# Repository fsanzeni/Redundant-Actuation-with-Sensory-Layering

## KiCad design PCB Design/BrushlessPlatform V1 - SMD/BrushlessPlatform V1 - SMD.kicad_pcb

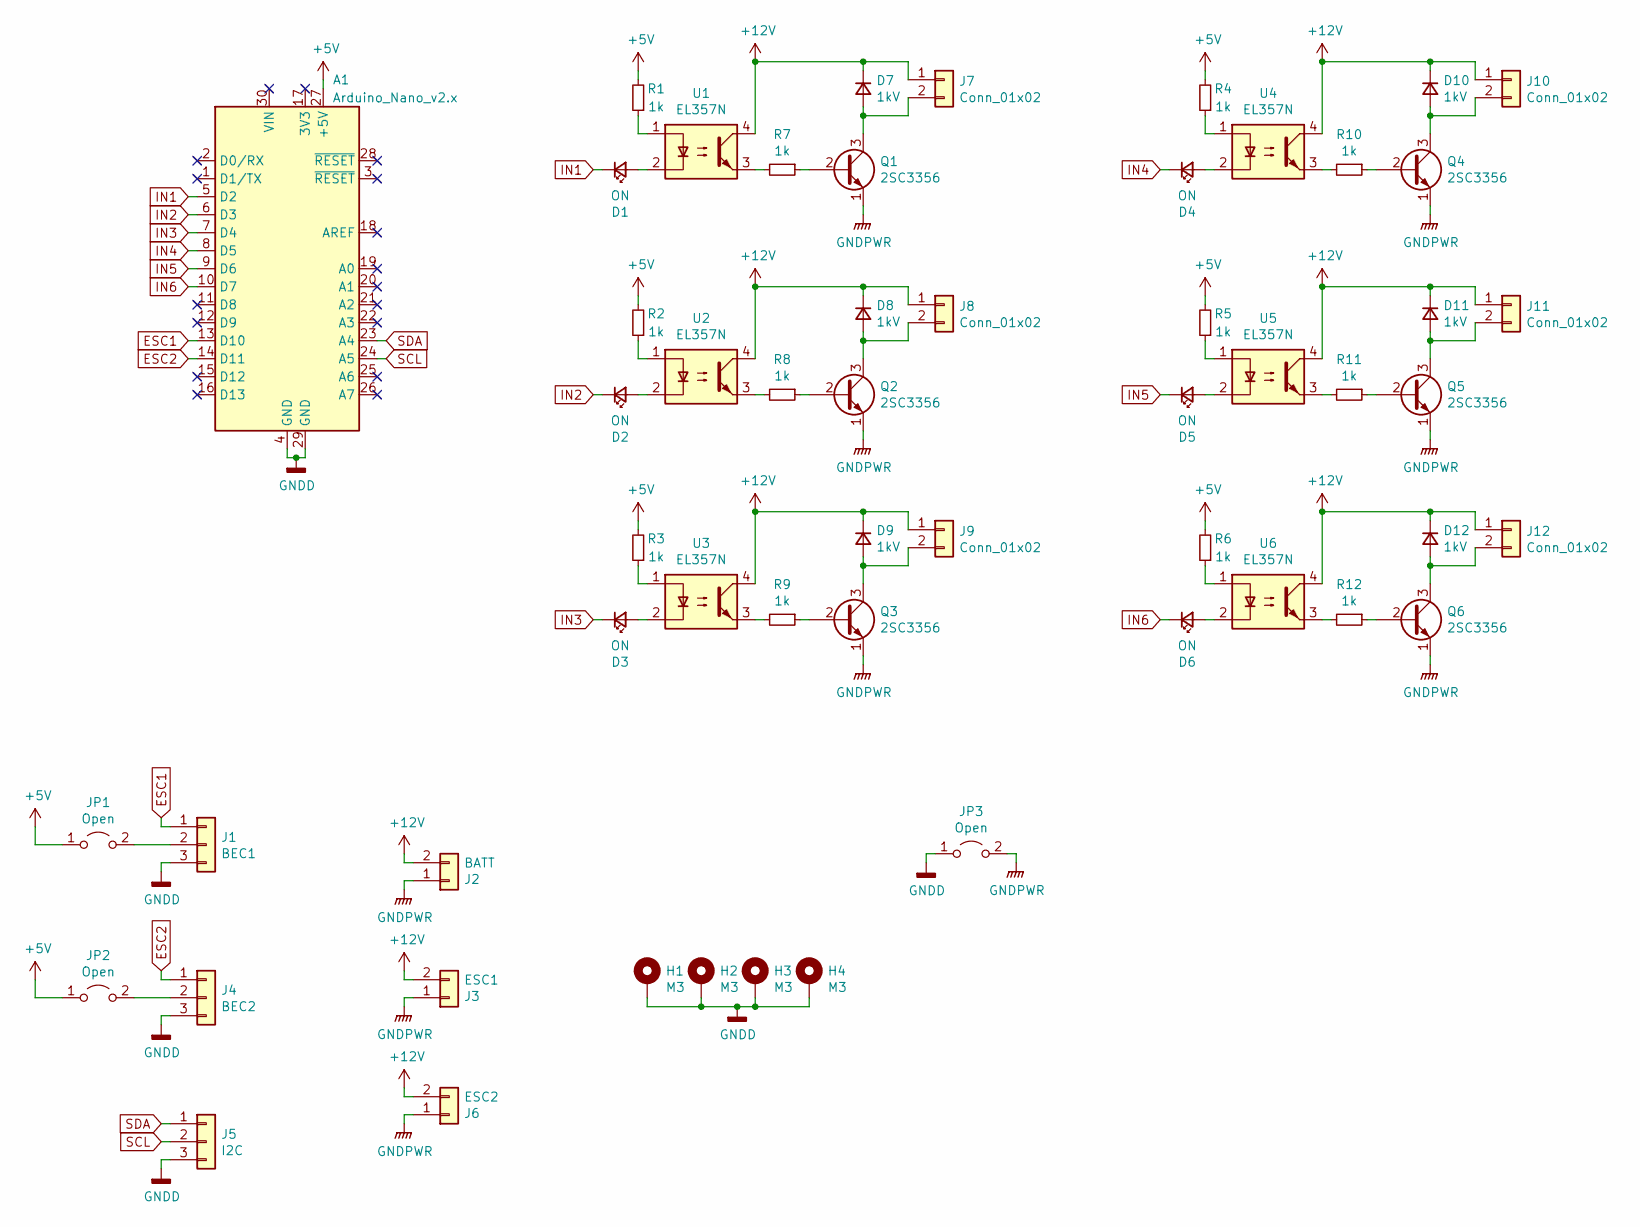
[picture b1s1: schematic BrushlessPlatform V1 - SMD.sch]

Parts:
A1: Arduino_Nano_v2.x; Arduino_Nano
D1, D2, D3, D4, D5, D6: ON; LED_0603_1608Metric
D7, D8, D9, D10, D11, D12: 1kV; D_SMA
H1, H2, H3, H4: M3; MountingHole_3.2mm_M3_ISO7380_Pad
J1: BEC1; PinSocket_1x03_P2.54mm_Vertical
J2: BATT; AMASS_XT60-M_1x02_P7.20mm_Vertical
J3: ESC1; AMASS_XT60-M_1x02_P7.20mm_Vertical
J4: BEC2; PinSocket_1x03_P2.54mm_Vertical
J5: I2C; PinSocket_1x03_P2.54mm_Vertical
J6: ESC2; AMASS_XT60-M_1x02_P7.20mm_Vertical
J7, J8, J9, J10, J11, J12: Conn_01x02; SolderWire-0.75sqmm_1x02_P4.8mm_D1.25mm_OD2.3mm_Relief
JP1, JP2, JP3: Open; SolderJumper-2_P1.3mm_Open_Pad1.0x1.5mm
Q1, Q2, Q3, Q4, Q5, Q6: 2SC3356; SOT-23
R1, R2, R3, R4, R5, R6, R7, R8, R9, R10, R11, R12: 1k; R_0603_1608Metric
U1, U2, U3, U4, U5, U6: EL357N; SOP-4_4.1x4.4x2.54P

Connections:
+5V: A1.27 (+5V), JP1.1 (A), JP2.1 (A), R1.2, R2.2, R3.2, R4.2, R5.2, R6.2
ESC1: A1.13 (D10), J1.1
ESC2: A1.14 (D11), J4.1
GNDD: A1.4 (GND), A1.29 (GND), H1.1, H2.1, H3.1, H4.1, J1.3, J4.3, J5.3, JP3.1 (A)
IN1: A1.5 (D2), D1.1 (K)
IN2: A1.6 (D3), D2.1 (K)
IN3: A1.7 (D4), D3.1 (K)
IN4: A1.8 (D5), D4.1 (K)
IN5: A1.9 (D6), D5.1 (K)
IN6: A1.10 (D7), D6.1 (K)
unnamed: D1.2 (A), U1.2
unnamed: D2.2 (A), U2.2
unnamed: D3.2 (A), U3.2
unnamed: D4.2 (A), U4.2
unnamed: D5.2 (A), U5.2
unnamed: D6.2 (A), U6.2
unnamed: D7.2 (A), J7.2, Q1.3 (C)
unnamed: D8.2 (A), J8.2, Q2.3 (C)
unnamed: D9.2 (A), J9.2, Q3.3 (C)
unnamed: D10.2 (A), J10.2, Q4.3 (C)
unnamed: D11.2 (A), J11.2, Q5.3 (C)
unnamed: D12.2 (A), J12.2, Q6.3 (C)
unnamed: J1.2, JP1.2 (B)
unnamed: J4.2, JP2.2 (B)
unnamed: Q1.2 (B), R7.1
unnamed: Q2.2 (B), R8.1
unnamed: Q3.2 (B), R9.1
unnamed: Q4.2 (B), R10.1
unnamed: Q5.2 (B), R11.1
unnamed: Q6.2 (B), R12.1
unnamed: R1.1, U1.1
unnamed: R2.1, U2.1
unnamed: R3.1, U3.1
unnamed: R4.1, U4.1
unnamed: R5.1, U5.1
unnamed: R6.1, U6.1
unnamed: R7.2, U1.3
unnamed: R8.2, U2.3
unnamed: R9.2, U3.3
unnamed: R10.2, U4.3
unnamed: R11.2, U5.3
unnamed: R12.2, U6.3
SCL: A1.24 (A5), J5.2
SDA: A1.23 (A4), J5.1

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
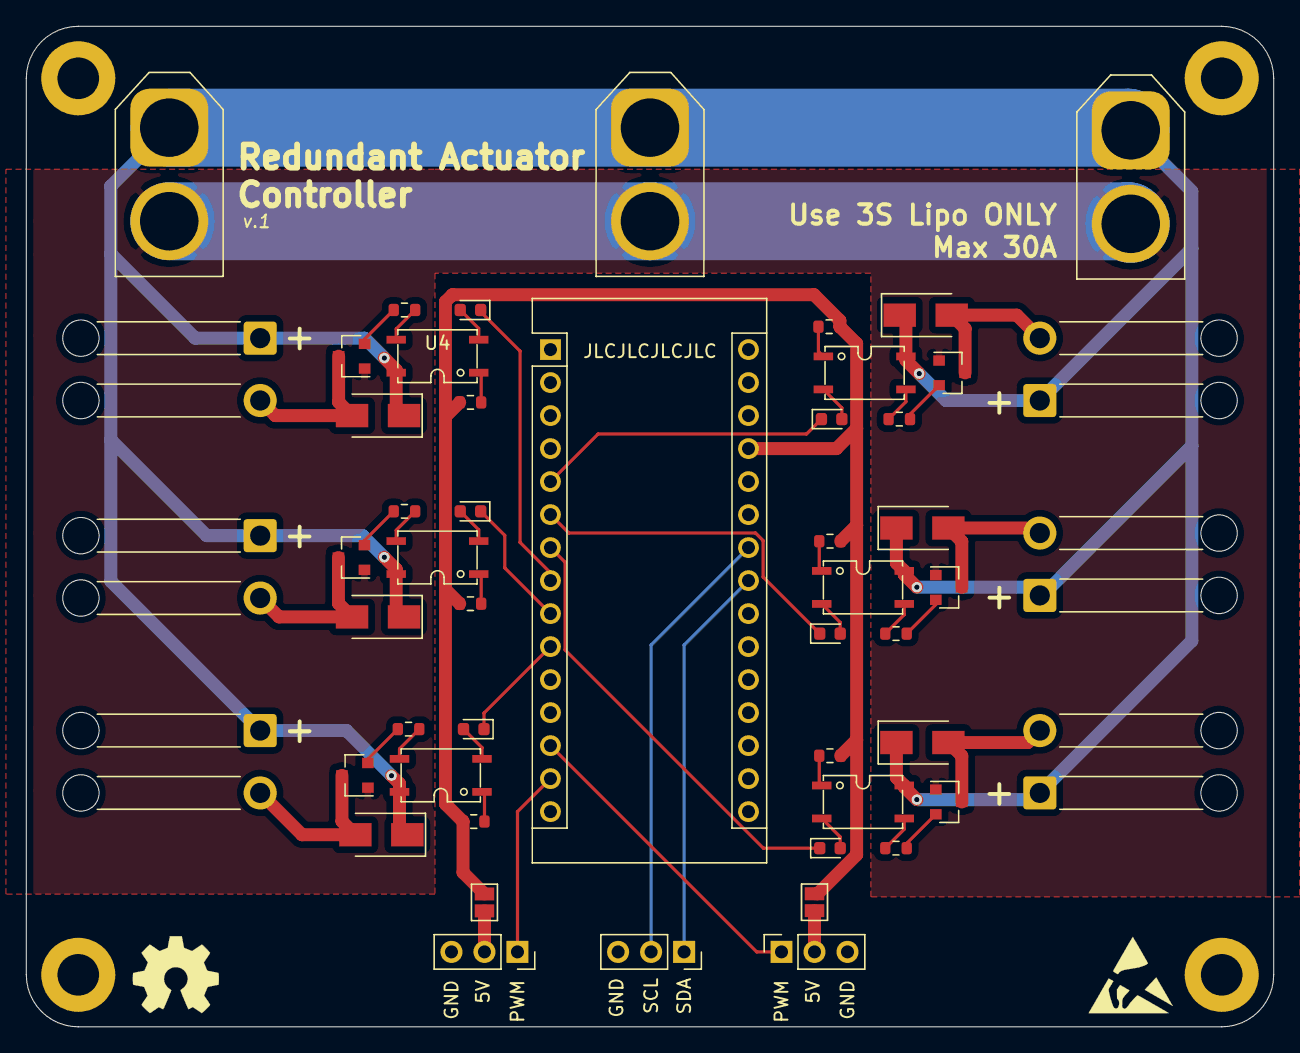
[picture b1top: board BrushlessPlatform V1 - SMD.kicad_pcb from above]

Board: 2 copper layers, 96.0 x 77.0 mm, 55 parts (0 on the bottom side), 46 nets.

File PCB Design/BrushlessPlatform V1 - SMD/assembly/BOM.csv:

Designator,Quantity,Value,Footprint,LCSC Part #,
"D1, D2, D3, D4, D5, D6, ",6,ON,0603,C72043,
"D7, D8, D9, D10, D11, D12, ",6,1kV,"SMA,DO-214AC",C412437,
"Q1, Q2, Q3, Q4, Q5, Q6, ",6,2SC3356,SOT-23-3,C9659,
"R1, R2, R3, R4, R5, R6, R7, R8, R9, R10, R11, R12, ",12,1k,0603,C21190,
"U1, U2, U3, U4, U5, U6, ",6,EL357N,SOP-4_4.1x4.4x2.54P,C6649,
,,,,,

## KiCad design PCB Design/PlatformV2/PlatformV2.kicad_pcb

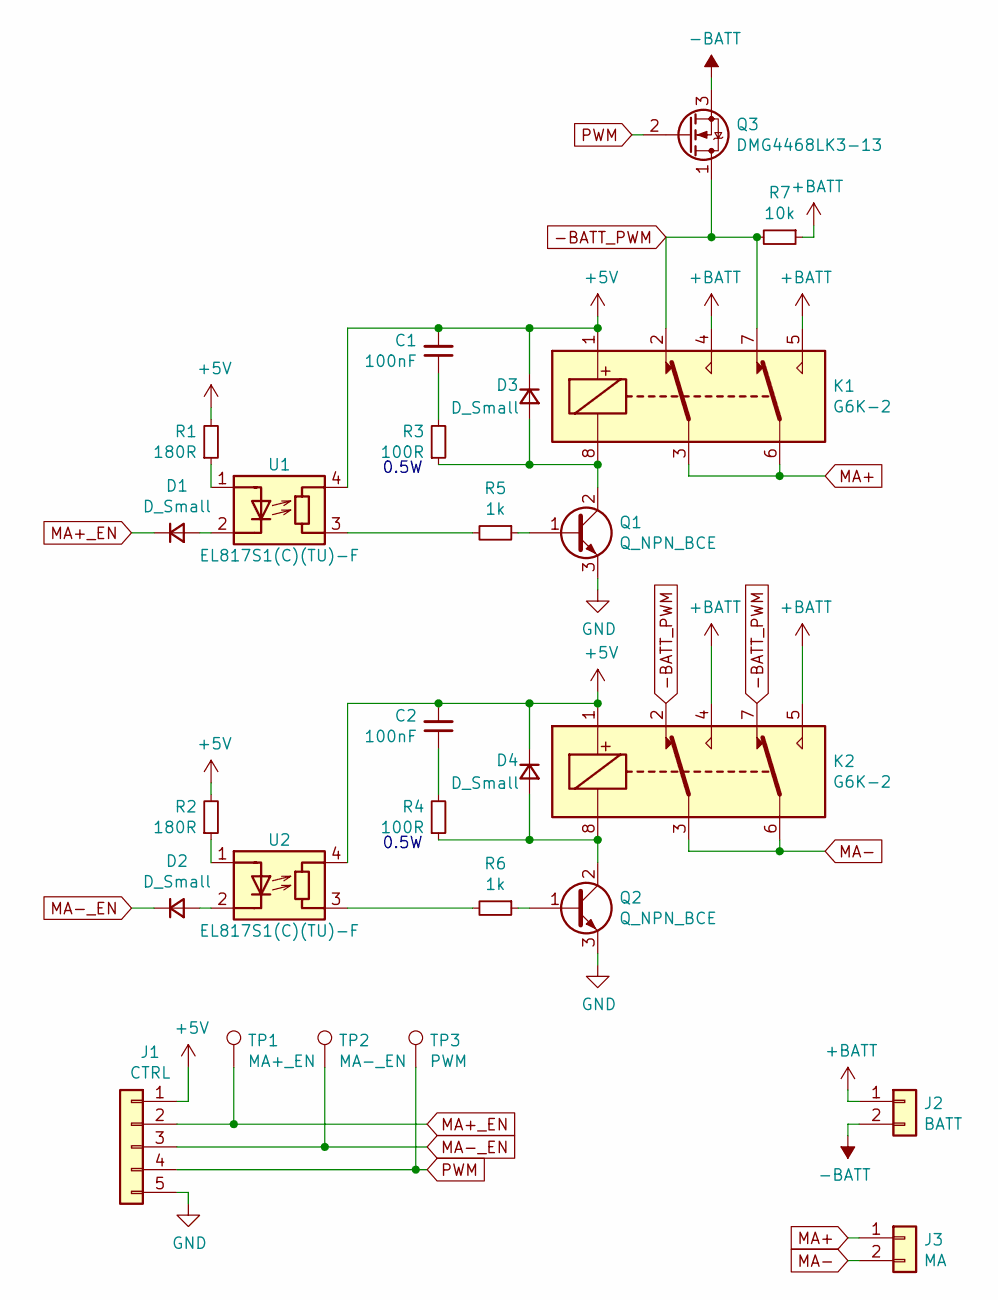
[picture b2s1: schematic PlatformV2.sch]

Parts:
C1, C2: 100nF; C_0805_2012Metric
D1, D2: D_Small; D_SOD-323F
D3, D4: D_Small; D_SMA
J1: CTRL; PinSocket_1x05_P2.54mm_Vertical
J2: BATT; PinSocket_1x02_P2.54mm_Vertical
J3: MA; PinSocket_1x02_P2.54mm_Vertical
K1, K2: G6K-2; G6K-2F_DC5
Q1, Q2: Q_NPN_BCE; SOT-23
Q3: DMG4468LK3-13; TO-252-2
R1, R2: 180R; R_0603_1608Metric
R3, R4: 100R; R_0603_1608Metric
R5, R6: 1k; R_0603_1608Metric
R7: 10k; R_0603_1608Metric
TP1: MA+_EN; TestPoint_Pad_D1.0mm
TP2: MA-_EN; TestPoint_Pad_D1.0mm
TP3: PWM; TestPoint_Pad_D1.0mm
U1, U2: EL817S1(C)(TU)-F

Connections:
+5V: C1.2, C2.2, D3.1 (K), D4.1 (K), J1.1, K1.1, K2.1, R1.2, R2.2, U1.4 (R), U2.4 (R)
+BATT: J2.1, K1.4, K1.5, K2.4, K2.5, R7.1
-BATT: J2.2, Q3.3 (S)
-BATT_PWM: K1.2, K1.7, K2.2, K2.7, Q3.1 (D), R7.2
GND: J1.5, Q1.3 (E), Q2.3 (E)
MA+: J3.1, K1.3, K1.6
MA+_EN: D1.1 (K), J1.2, TP1.1
MA-: J3.2, K2.3, K2.6
MA-_EN: D2.1 (K), J1.3, TP2.1
unnamed: C1.1, R3.2
unnamed: C2.1, R4.2
unnamed: D1.2 (A), U1.2 (K)
unnamed: D2.2 (A), U2.2 (K)
unnamed: D3.2 (A), K1.8, Q1.2 (C), R3.1
unnamed: D4.2 (A), K2.8, Q2.2 (C), R4.1
unnamed: Q1.1 (B), R5.1
unnamed: Q2.1 (B), R6.1
unnamed: R1.1, U1.1 (A)
unnamed: R2.1, U2.1 (A)
unnamed: R5.2, U1.3 (R)
unnamed: R6.2, U2.3 (R)
PWM: J1.4, Q3.2 (G), TP3.1

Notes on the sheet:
0.5W

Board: 2 copper layers, 26 parts (0 on the bottom side), 22 nets, no tracks yet.

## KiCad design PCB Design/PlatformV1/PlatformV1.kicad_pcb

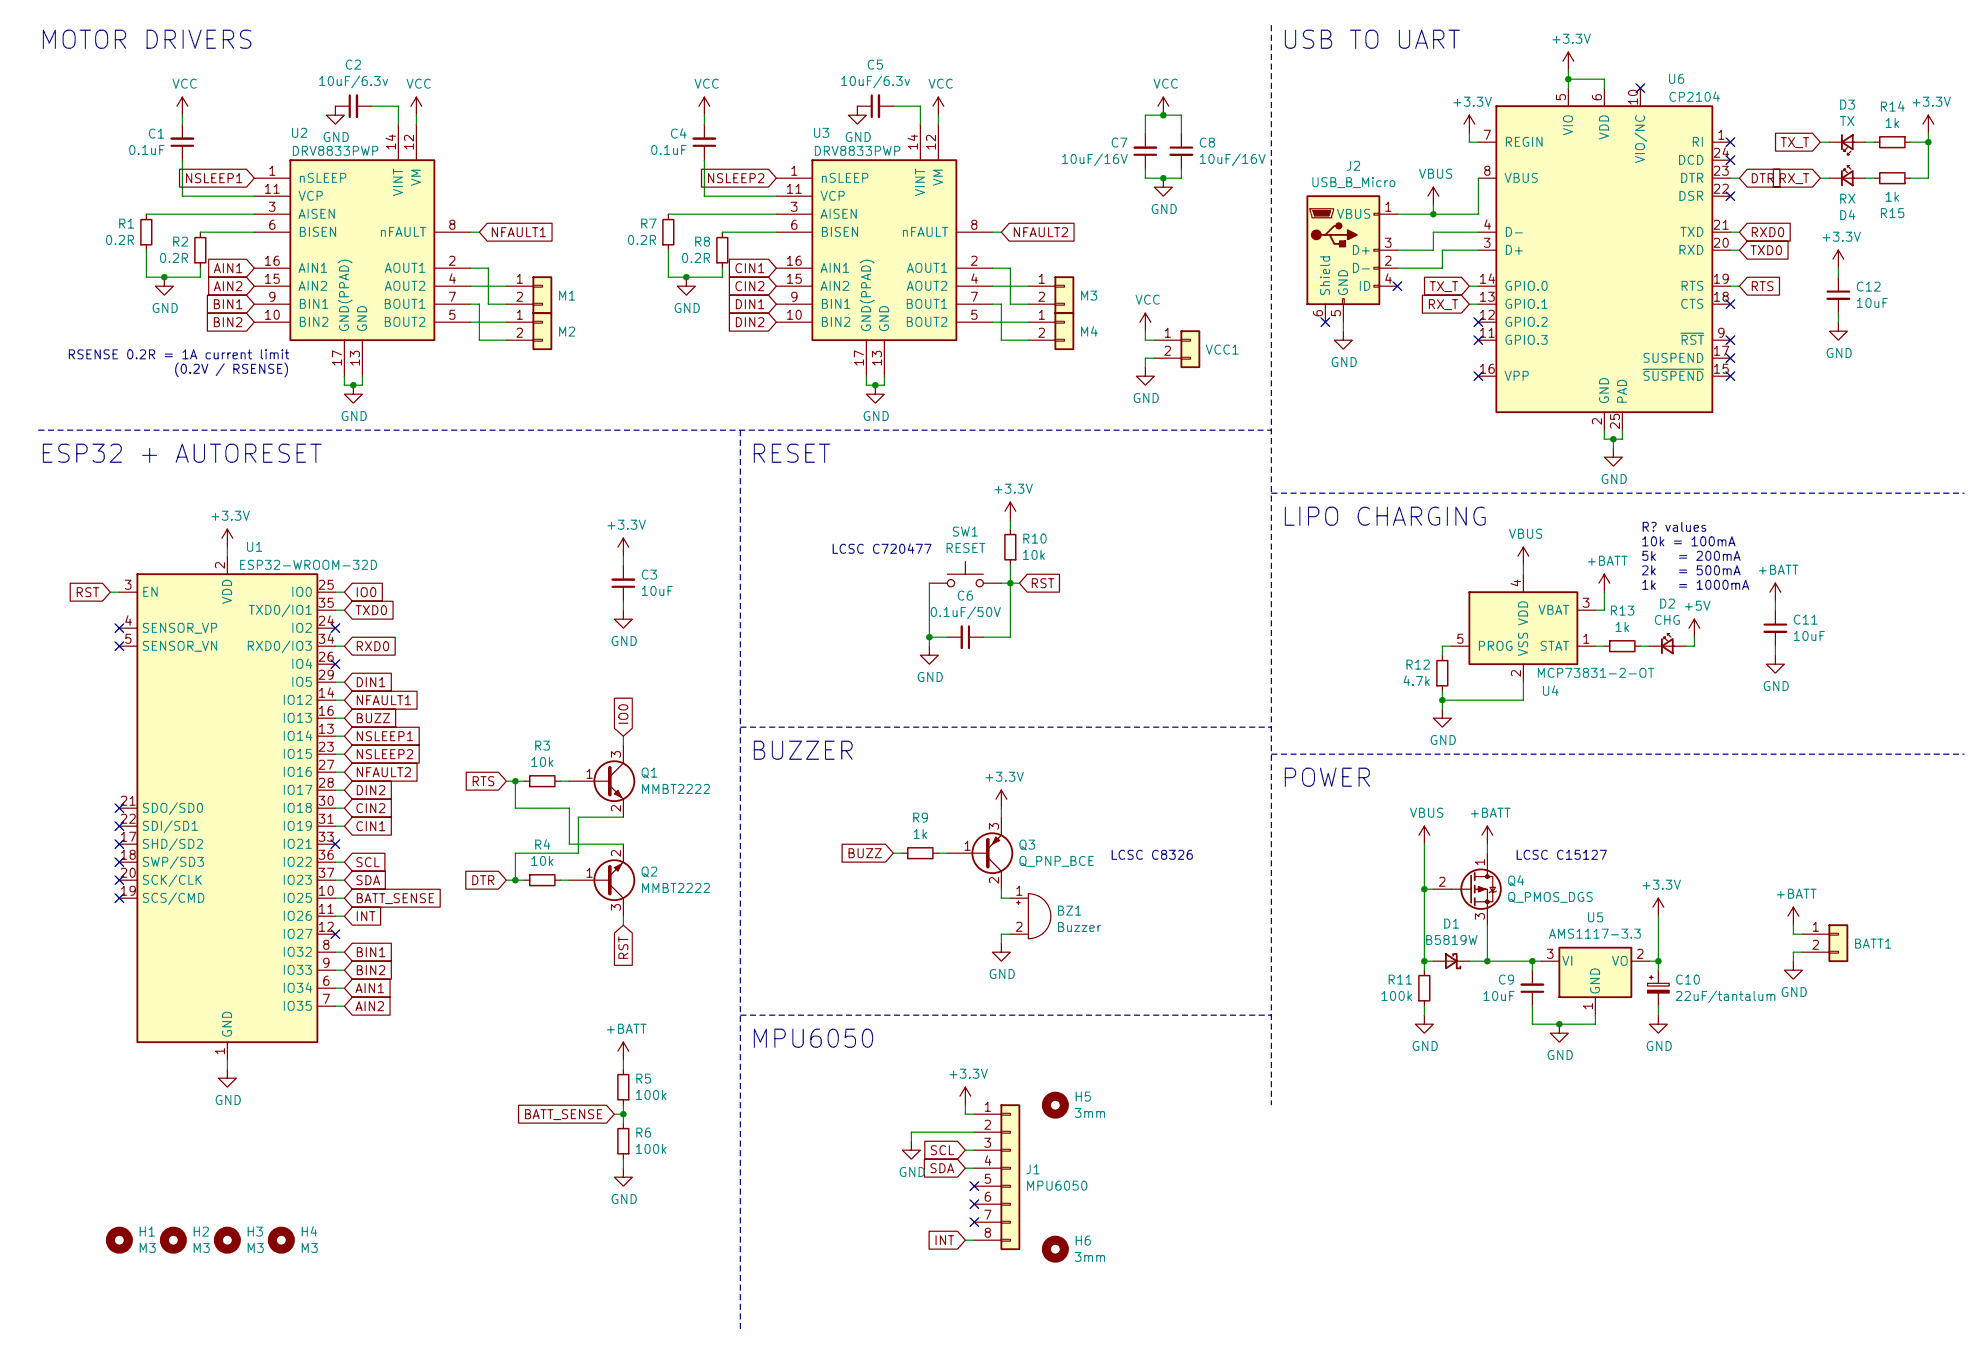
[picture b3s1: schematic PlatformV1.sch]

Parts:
BATT1: Conn_01x02; PinSocket_1x02_P2.54mm_Vertical
BZ1: Buzzer; Buzzer_12x9.5RM7.6
C1, C4: 0.1uF; C_0603_1608Metric
C2, C5: 10uF/6.3v; C_0603_1608Metric
C3, C9, C11, C12: 10uF; C_0603_1608Metric
C6: 0.1uF/50V; C_0603_1608Metric
C7, C8: 10uF/16V; C_1206_3216Metric
C10: 22uF/tantalum; CP_EIA-3216-18_Kemet-A
D1: B5819W; D_SOD-123
D2: CHG; LED_0603_1608Metric
D3: TX; LED_0603_1608Metric
D4: RX; LED_0603_1608Metric
H1, H2, H3, H4: M3; MountingHole_3.2mm_M3
H5, H6: 3mm; MountingHole_3mm
J1: MPU6050; PinSocket_1x08_P2.54mm_Vertical
J2: USB_B_Micro; USB_Micro-B_Amphenol_10103594-0001LF_Horizontal
M1, M2, M3, M4: Conn_01x02; PinSocket_1x02_P2.54mm_Vertical
Q1, Q2: MMBT2222; SOT-23
Q3: Q_PNP_BCE; SOT-23
Q4: Q_PMOS_DGS; SOT-23
R1, R2, R7, R8: 0.2R; R_1206_3216Metric
R3, R4, R10: 10k; R_0603_1608Metric
R5, R6, R11: 100k; R_0603_1608Metric
R9, R13, R14, R15: 1k; R_0603_1608Metric
R12: 4.7k; R_0603_1608Metric
SW1: RESET; SW_Push_1P1T_NO_6x6mm_H9.5mm
U1: ESP32-WROOM-32D; ESP32-WROOM-32
U2, U3: DRV8833PWP; HTSSOP-16-1EP_4.4x5mm_P0.65mm_EP3.4x5mm_Mask2.46x2.31mm_The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
U4: MCP73831-2-OT; SOT-23-5
U5: AMS1117-3.3; SOT-223-3_TabPin2
U6: CP2104; QFN-24-1EP_4x4mm_P0.5mm_EP2.6x2.6mm
VCC1: Conn_01x02; PinSocket_1x02_P2.54mm_Vertical

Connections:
+3V3: C3.2, C10.1, C12.1, J1.1, Q3.3 (E), R10.2, R14.1, R15.1, U1.2 (VDD), U5.2 (VO), U6.5 (VIO), U6.6 (VDD), U6.7 (REGIN)
+5V: D2.2 (A)
+BATT: BATT1.1, C11.1, Q4.1 (D), R5.2, U4.3 (VBAT)
AIN1: U1.6 (IO34), U2.16 (AIN1)
AIN2: U1.7 (IO35), U2.15 (AIN2)
BATT_SENSE: R5.1, R6.2, U1.10 (IO25)
BIN1: U1.8 (IO32), U2.9 (BIN1)
BIN2: U1.9 (IO33), U2.10 (BIN2)
BUZZ: R9.1, U1.16 (IO13)
CIN1: U1.31 (IO19), U3.16 (AIN1)
CIN2: U1.30 (IO18), U3.15 (AIN2)
DIN1: U1.29 (IO5), U3.9 (BIN1)
DIN2: U1.28 (IO17), U3.10 (BIN2)
DTR: Q1.2 (E), R4.1, U6.23 (DTR)
GND: BATT1.2, BZ1.2 (+), C2.1, C3.1, C5.1, C6.2, C7.1, C8.2, C9.1, C10.2, C11.2, C12.2, J1.2, J2.5 (GND), R1.1, R2.1, R6.1, R7.1, R8.1, R11.1, R12.1, SW1.1, U1.1 (GND), U1.15 (GND), U1.38 (GND), U1.39 (GND), U2.13 (GND), U2.17 (GND(PPAD)), U3.13 (GND), U3.17 (GND(PPAD)), U4.2 (VSS), U5.1 (GND), U6.2 (GND), U6.25 (PAD), VCC1.2
INT: J1.8, U1.11 (IO26)
IO0: Q1.3 (C), U1.25 (IO0)
NFAULT1: U1.14 (IO12), U2.8 (nFAULT)
NFAULT2: U1.27 (IO16), U3.8 (nFAULT)
NSLEEP1: U1.13 (IO14), U2.1 (nSLEEP)
NSLEEP2: U1.23 (IO15), U3.1 (nSLEEP)
unnamed: BZ1.1 (-), Q3.2 (C)
unnamed: C1.1, U2.11 (VCP)
unnamed: C2.2, U2.14 (VINT)
unnamed: C4.1, U3.11 (VCP)
unnamed: C5.2, U3.14 (VINT)
unnamed: C9.2, D1.1 (K), Q4.3 (S), U5.3 (VI)
unnamed: D2.1 (K), R13.2
unnamed: D3.2 (A), R14.2
unnamed: D4.2 (A), R15.2
unnamed: J2.2 (D-), U6.3 (D+)
unnamed: J2.3 (D+), U6.4 (D-)
unnamed: M1.1, U2.4 (AOUT2)
unnamed: M1.2, U2.2 (AOUT1)
unnamed: M2.1, U2.5 (BOUT2)
unnamed: M2.2, U2.7 (BOUT1)
unnamed: M3.1, U3.4 (AOUT2)
unnamed: M3.2, U3.2 (AOUT1)
unnamed: M4.1, U3.5 (BOUT2)
unnamed: M4.2, U3.7 (BOUT1)
unnamed: Q1.1 (B), R3.2
unnamed: Q2.1 (B), R4.2
unnamed: Q3.1 (B), R9.2
unnamed: R1.2, U2.3 (AISEN)
unnamed: R2.2, U2.6 (BISEN)
unnamed: R7.2, U3.3 (AISEN)
unnamed: R8.2, U3.6 (BISEN)
unnamed: R12.2, U4.5 (PROG)
unnamed: R13.1, U4.1 (STAT)
RST: C6.1, Q2.3 (C), R10.1, SW1.2, U1.3 (EN)
RTS: Q2.2 (E), R3.1, U6.19 (RTS)
RXD0: U1.34 (RXD0/IO3), U6.21 (TXD)
RX_T: D4.1 (K), U6.13 (GPIO.1)
SCL: J1.3, U1.36 (IO22)
SDA: J1.4, U1.37 (IO23)
TXD0: U1.35 (TXD0/IO1), U6.20 (RXD)
TX_T: D3.1 (K), U6.14 (GPIO.0)
VBUS: D1.2 (A), J2.1 (VBUS), Q4.2 (G), R11.2, U4.4 (VDD), U6.8 (VBUS)
VCC: C1.2, C4.2, C7.2, C8.1, U2.12 (VM), U3.12 (VM), VCC1.1

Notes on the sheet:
RSENSE 0.2R = 1A current limit (0.2V / RSENSE)
MOTOR DRIVERS
USB TO UART
R? values 10k = 100mA 5k = 200mA 2k = 500mA 1k = 1000mA
LIPO CHARGING
ESP32 + AUTORESET
RESET
BUZZER
POWER
MPU6050
LCSC C720477
LCSC C8326
LCSC C15127

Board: 2 copper layers, 57 parts (0 on the bottom side), 58 nets, no tracks yet.

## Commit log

2023-04-23 Initial commit
    readme missing - will add after submission
